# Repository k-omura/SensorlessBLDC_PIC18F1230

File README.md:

# Sensorless BLDC Driver
Sensorless brushless motor controller using PIC18F1230 (XC8)  
* Use only PIC and FET  
* PWM  
* ADC  

-------------------------------------------
# Features(Implemented)  
* Open-loop drive.  
* Closed-loop drive(seamless transfer from open-loop).  
* Closed-loop lock detection(back to open-loop).  
* Speed control by EUSART input.  

-------------------------------------------
# Variables(Implemented)  
* Direction of rotation  
* Open-loop duty  
* Open-loop initial speed  
* Open-loop acceleration  
* Open-loop to closed-loop speed  
* Closed-loop speed  
* Closed-loop acceleration  

-------------------------------------------
# My parts list  
PIC: PIC18F1230 http://ww1.microchip.com/downloads/en/DeviceDoc/39758D.pdf  
NPN Tr: 2SC1815  
MOSFET: SLA5064 http://www.semicon.sanken-ele.co.jp/sk_content/sla5064_ds_en.pdf  
Motor : A2212 13T 950kV/1000kV/1300kV/2300kV, Tarot 4006 620kV  

-------------------------------------------
# Videos  
Closed-loop test: https://youtu.be/z_nNao-uBho  
Lock detection test: https://youtu.be/O4YZ754I2WM  
EUSART speed input with foot pedal: https://youtu.be/TU5dIhgWp5A  

-------------------------------------------
# How to use  
1. install MPLAB X / XC8  
2. create PIC18F1230 project  
3. create main.c in "Source Files"  
4. copy one of the main(---).c  
5. Write it  

-------------------------------------------
This is a part of the quadcopter making project.

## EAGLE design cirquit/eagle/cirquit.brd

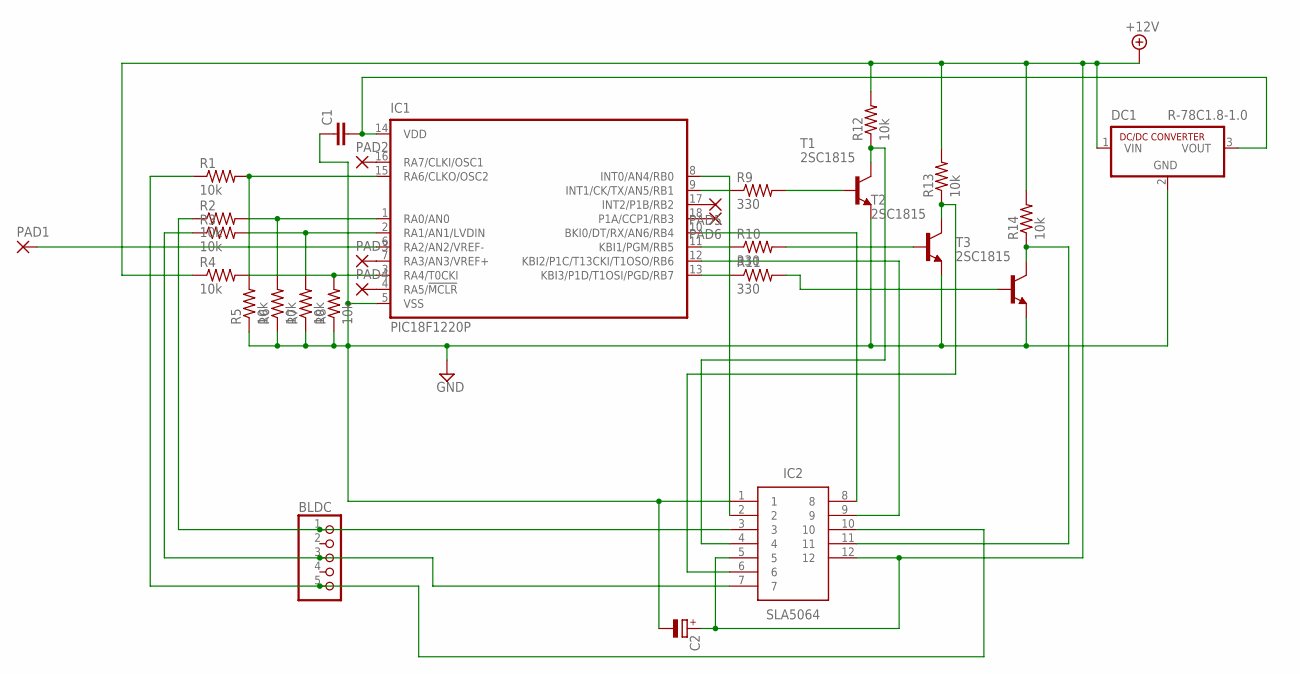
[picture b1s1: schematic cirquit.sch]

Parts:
BLDC: PINHD-1X5; 1X05
C1: C2.5/2; C2.5-2
C2: CPOL-EUE2,5-6E; E2,5-6E
DC1: R-78C1.8-1.0; SIP3
IC1: PIC18F1220P; DIL18
IC2: SLA5064; TO254P500X3150X1890-12P
PAD1, PAD2, PAD3, PAD4, PAD5, PAD6: 1,6/0,8
R1, R2, R3, R4, R5, R6, R7, R8, R12, R13, R14: 10k; 0204/7
R9, R10, R11: 330; 0204/7
T1, T2, T3: 2SC1815; TO92-ECB

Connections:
+12V: C2.+, DC1.1 (VIN), IC2.5, IC2.12, R4.1, R12.2, R13.2, R14.2
GND: C1.1, C2.-, DC1.2 (GND), IC1.5 (VSS), IC2.1, R5.1, R6.1, R7.1, R8.1, T1.E, T2.E, T3.E
unnamed: IC1.15 (RA6/CLKO/OSC2), R1.2, R5.2
unnamed: IC1.1 (RA0/AN0), R2.2, R6.2
unnamed: IC1.2 (RA1/AN1/LVDIN), R3.2, R7.2
unnamed: IC1.3 (RA4/T0CKI), R4.2, R8.2
unnamed: IC1.16 (RA7/CLKI/OSC1), PAD2.1
unnamed: BLDC.1, IC2.3, R2.1
unnamed: BLDC.3, IC2.7, R3.1
unnamed: IC1.9 (INT1/CK/TX/AN5/RB1), R9.1
unnamed: IC1.11 (KBI1/PGM/RB5), R10.1
unnamed: IC1.13 (KBI3/P1D/T1OSI/PGD/RB7), R11.1
unnamed: R9.2, T1.B
unnamed: R10.2, T2.B
unnamed: R11.2, T3.B
unnamed: IC2.4, R12.1, T1.C
unnamed: IC2.6, R13.1, T2.C
unnamed: IC2.11, R14.1, T3.C
unnamed: IC1.7 (RA3/AN3/VREF+), PAD3.1
unnamed: IC1.4 (RA5/!MCLR), PAD4.1
unnamed: IC1.17 (INT2/P1B/RB2), PAD5.1
unnamed: IC1.18 (P1A/CCP1/RB3), PAD6.1
unnamed: IC1.8 (INT0/AN4/RB0), IC2.2
unnamed: IC1.10 (BKI0/DT/RX/AN6/RB4), IC2.8
unnamed: IC1.12 (KBI2/P1C/T13CKI/T1OSO/RB6), IC2.9
unnamed: IC1.6 (RA2/AN2/VREF-), PAD1.1
unnamed: C1.2, DC1.3 (VOUT), IC1.14 (VDD)
unnamed: BLDC.5, IC2.10, R1.1

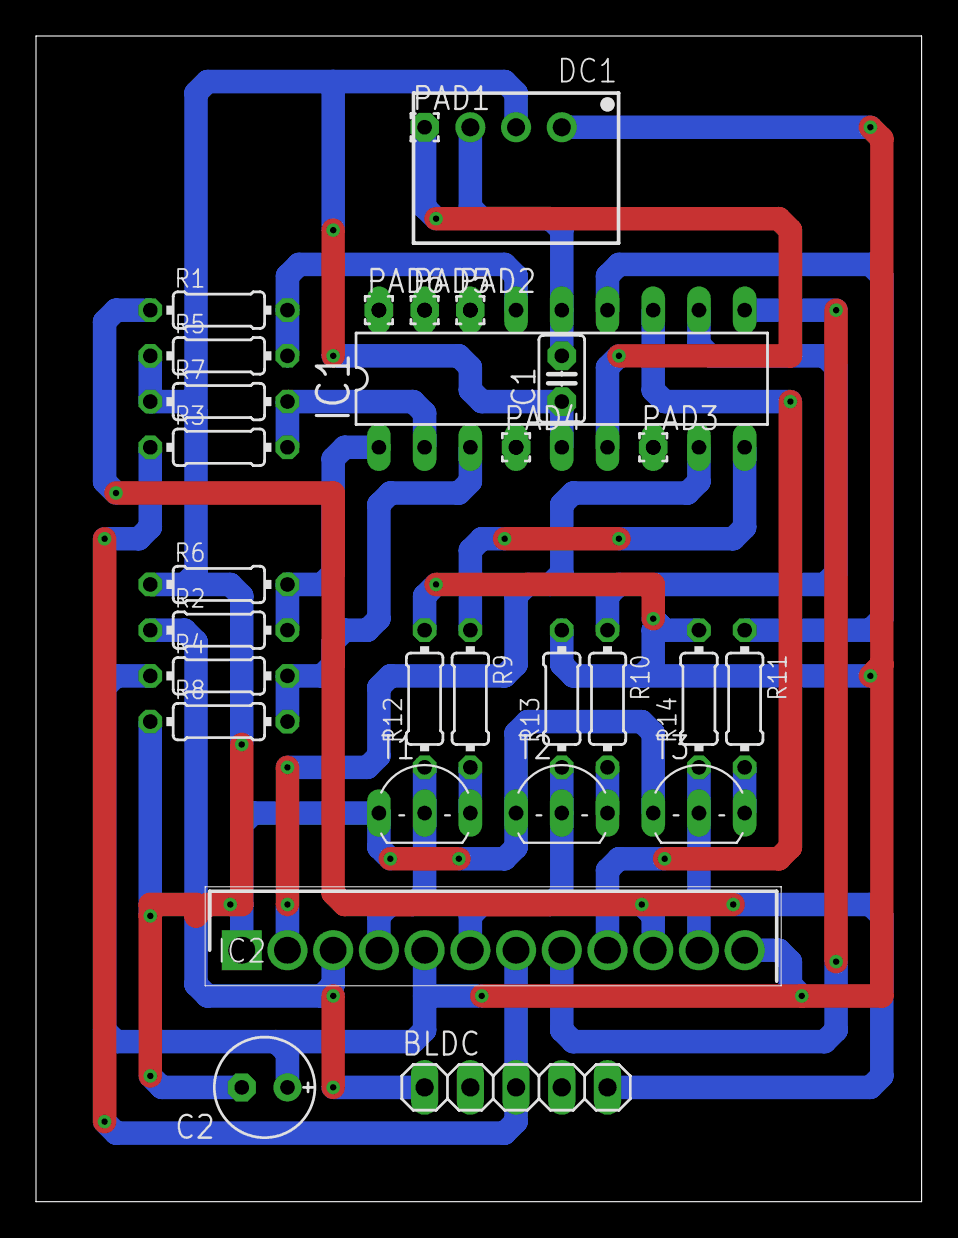
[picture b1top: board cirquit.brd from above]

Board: 2 copper layers, 49.2 x 64.8 mm, 29 parts (0 on the bottom side), 28 nets.

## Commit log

2017-09-10 open loop drive test completed
    feedback output does not work well
2017-09-11 Create a
2017-09-11 Change to make it easy to open to close control
    Detection is still not successful
2017-09-12 Closed Loop successfull
2017-09-13 Rename main.c to main(just-rotate).c
2017-09-13 Settled issue #3
    Seamless transition open to close
    +clean up the code
2017-09-13 Settled issue #2
    lock detect and re-transfer open-loop
2017-09-13 Rename main(just-rotate).c to main(just_rotate).c
2017-09-15 Non-blocking acceleration in closed-loop
2017-09-15 Nightly update.
    probably no trouble
2017-09-16 Create main(EUSART_speed_control).c
    EUSART input speed control.
    -Lower 2 bits: address
    -Upper 6 bits: speed data
2017-09-17 Create test
2017-09-17 Re-written in eagle
    For creating diagram by auto-route
2017-09-18 BLDC Driver wiring diagram
2018-01-01 Rename main(lock_detection).c to main(Set_speed_internally).c
2018-08-28 Create LICENSE
2018-09-20 Change to XC8 2.00, C99
2018-09-21 Review variable size
